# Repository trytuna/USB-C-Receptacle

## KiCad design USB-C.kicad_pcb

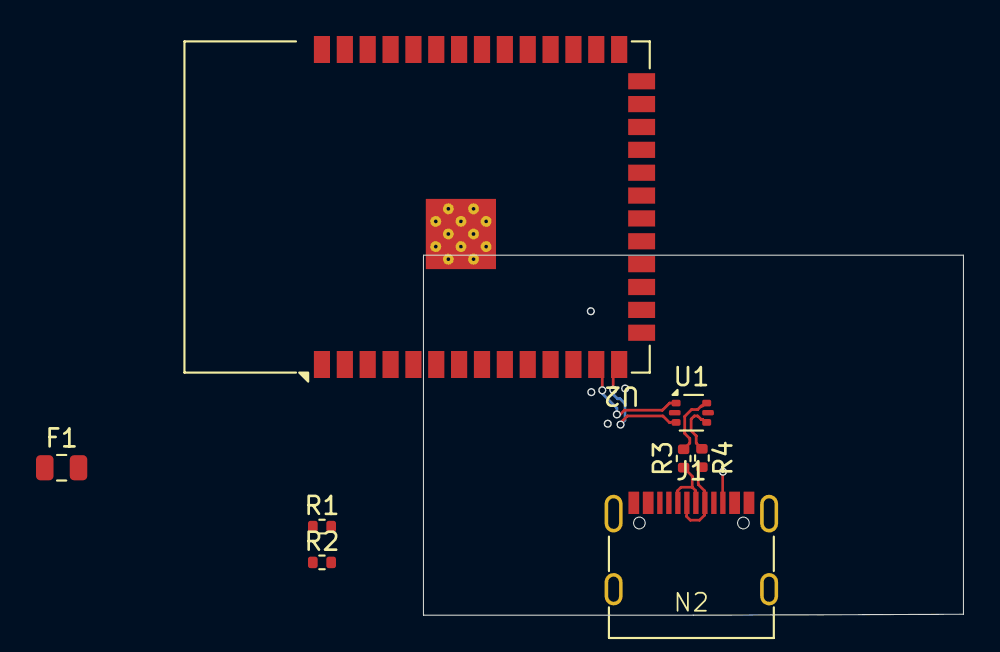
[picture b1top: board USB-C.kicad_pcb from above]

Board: 4 copper layers, 30.0 x 20.0 mm, 8 parts (0 on the bottom side), 12 nets.

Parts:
F1: 500mA; Fuse_0805_2012Metric
J1: USB_C_Receptacle; USB_C_Receptacle_G-Switch_GT-USB-7010ASV
R1, R2: 5k1; R_0402_1005Metric
R3, R4: 22; R_0402_1005Metric
U1: USBLC6-2P6; SOT-666
U2: ESP32-S3-WROOM-1

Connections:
+5V: F1.1, U1.5 (VBUS)
/D+: R4.1, U1.4 (I/O2)
/D-: R3.2, U1.6 (I/O1)
GND: J1.A1 (GND), J1.A12 (GND), J1.B1 (GND), J1.B12 (GND), J1.S1 (SHIELD), R1.1, R2.1, U1.2 (GND)
unnamed: F1.2, J1.A4 (VBUS), J1.A9 (VBUS), J1.B4 (VBUS), J1.B9 (VBUS)
unnamed: J1.A5 (CC1), R1.2
unnamed: J1.B5 (CC2), R2.2
unnamed: J1.A6 (D+), J1.B6 (D+), R4.2
unnamed: J1.A7 (D-), J1.B7 (D-), R3.1
unnamed: U2.1 (GND), U2.40 (GND), U2.41 (GND)
USB_D_N: U1.1 (I/O1), U2.13 (USB_D-)
USB_D_P: U1.3 (I/O2), U2.14 (USB_D+)

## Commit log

2025-01-30 Add images
2025-01-30 Fix filename
2025-01-30 Demoday
